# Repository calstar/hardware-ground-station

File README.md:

View this project on [CADLAB.io](https://cadlab.io/project/22830). 

# hardware-ground-station

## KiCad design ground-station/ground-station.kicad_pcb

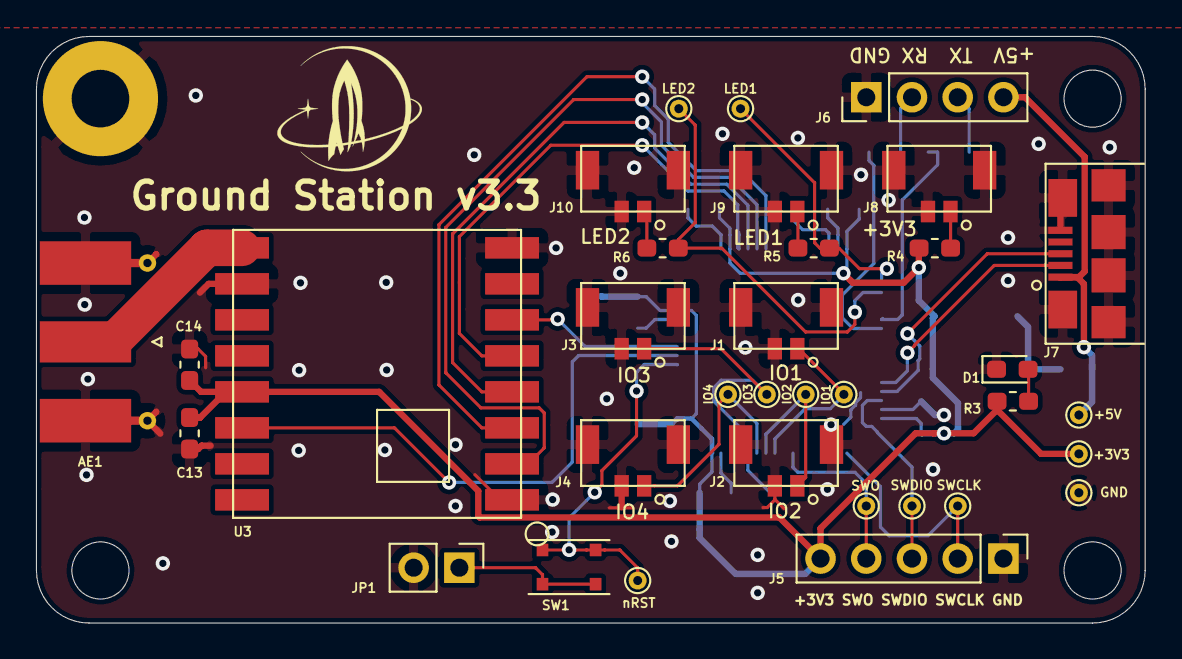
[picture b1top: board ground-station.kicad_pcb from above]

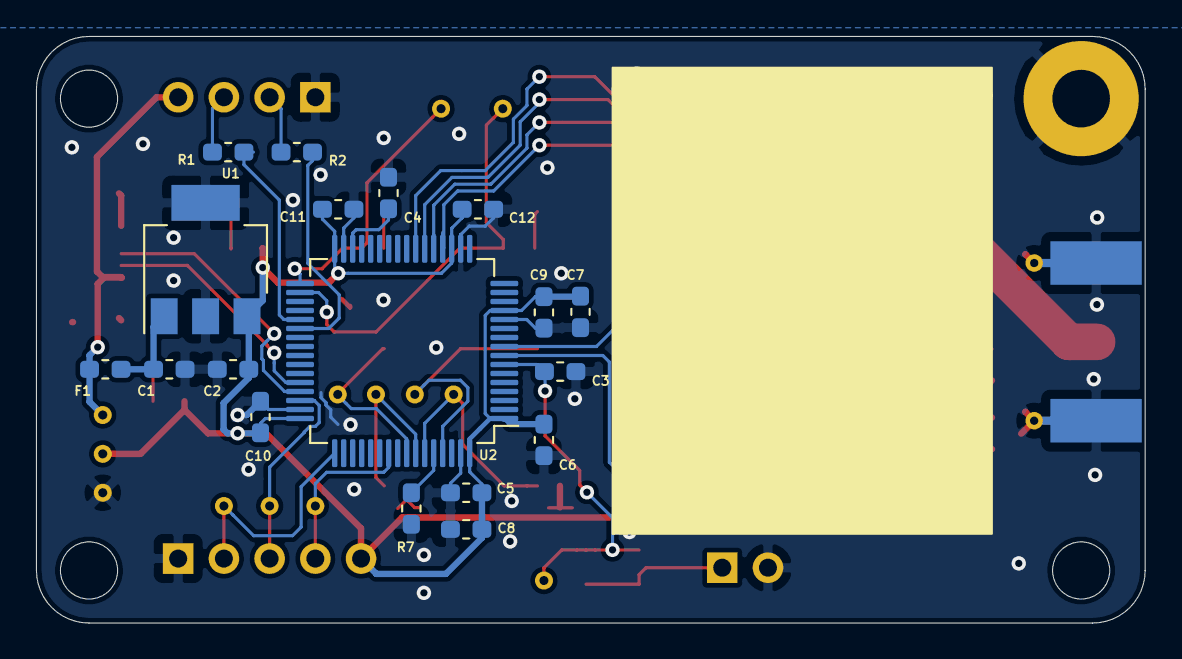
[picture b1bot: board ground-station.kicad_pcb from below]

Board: 2 copper layers, 61.6 x 32.6 mm, 53 parts (18 on the bottom side), 34 nets.

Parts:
AE1: Antenna_Dipole; SMA_Molex_73251-1153_EdgeMount_Horizontal
C1: 0.47uF; C_0603_1608Metric_Pad1.05x0.95mm_HandSolder
C2: 47uF; C_0603_1608Metric_Pad1.05x0.95mm_HandSolder
C3, C6, C7, C8, C10, C11, C12, C14: 0.1uF; C_0603_1608Metric_Pad1.05x0.95mm_HandSolder
C4: 4.7uF; C_0603_1608Metric_Pad1.05x0.95mm_HandSolder
C5, C13: 10uF; C_0603_1608Metric_Pad1.05x0.95mm_HandSolder
C9: 1uF; C_0603_1608Metric_Pad1.05x0.95mm_HandSolder
D1: LED; LED_0603_1608Metric_Pad1.05x0.95mm_HandSolder
F1: Fuse; Fuse_0603_1608Metric_Pad1.05x0.95mm_HandSolder
J1, J2, J3, J4, J8, J9, J10: Conn_01x02; Molex_Micro-Lock_505568-0271_1x02_P1.25mm_Vertical
J5: Conn_01x05; PinHeader_1x05_P2.54mm_Vertical
J6: Conn_01x04; PinHeader_1x04_P2.54mm_Vertical
J7: USB_B_Micro; USB_Micro-B_Amphenol_10118192-0001LF_Horizontal
JP1: Jumper; PinHeader_1x02_P2.54mm_Vertical
Mounting Hole: MountingHole_3.2mm_M3_Pad
R1, R2: 330; R_0603_1608Metric_Pad1.05x0.95mm_HandSolder
R3, R4, R5, R6: 68; R_0603_1608Metric_Pad1.05x0.95mm_HandSolder
R7: 10K; R_0603_1608Metric_Pad1.05x0.95mm_HandSolder
SW1: SW_Push; TE_Button_USLPT3026
TP1, TP2, TP3, TP4, TP13, TP14, TP15, TP16, TP17, TP18, TP19, TP20, TP21: TestPoint; TestPoint_THTPad_D1.0mm_Drill0.5mm
U1: LM3940; SOT-223
U2: STM32F401RETx; LQFP-64_10x10mm_P0.5mm
U3: RFM69HCW

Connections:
+3V3: C2.1, C5.1, C6.1, C7.1, C8.1, C9.1, C10.1, C11.1, C12.1, C13.1, C14.1, J5.5, R3.2, R4.2, TP3.1, U1.3, U2.1, U2.13, U2.19, U2.32, U2.48, U2.64, U3.13
+5V: F1.2, J6.4, J7.1, TP2.1
/RFM69HCW/ANT: AE1.1, U3.9
GND: AE1.2, C1.2, C2.2, C3.2, C4.2, C5.2, C6.2, C7.2, C8.2, C9.2, C10.2, C11.2, C12.2, C13.2, C14.2, D1.1, J1.2, J2.2, J3.2, J4.2, J5.1, J6.1, J7.5, J7.6, J8.2, J9.2, J10.2, JP1.2, Mounting Hole.1, R7.2, TP1.1, U1.2, U1.4, U2.12, U2.18, U2.31, U2.47, U2.63, U3.1, U3.8, U3.10
IO1: J1.1, TP18.1, U2.57
IO2: J2.1, TP19.1, U2.58
IO3: J3.1, TP20.1, U2.61
IO4: J4.1, TP21.1, U2.59
LED1: R5.2, TP16.1, U2.33
LED2: R6.2, TP17.1, U2.34
MCU_RX: R2.2, U2.38
MCU_TX: R1.2, U2.37
unnamed: C1.1, F1.1, U1.1
unnamed: C4.1, U2.30
unnamed: D1.2, R3.1
unnamed: J6.2, R2.1
unnamed: J6.3, R1.1
unnamed: J8.1, R4.1
unnamed: J9.1, R5.1
unnamed: J10.1, R6.1
unnamed: JP1.1, SW1.2
unnamed: R7.1, U2.60
OTG_FS_D+: J7.3, U2.45
OTG_FS_D-: J7.2, U2.44
RadioINT: U2.8, U3.14
RadioMISO: U2.22, U3.2
RadioMOSI: U2.23, U3.3
RadioRST: U2.9, U3.6
RadioSCK: U2.21, U3.4
RadionSS: U2.20, U3.5
SWCLK: J5.2, TP15.1, U2.49
SWDIO: J5.3, TP14.1, U2.46
SWO: J5.4, TP13.1, U2.55
nRST: C3.1, SW1.1, TP4.1, U2.7

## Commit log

2019-12-01 most of schematic
2019-12-01 Backlink to CADLAB.io has been added.
2019-12-01 added test points and organized schematic
2019-12-01 created footprints for rfm, usb micro b, and sma, and assigned all footprints
2019-12-08 lots of work on layout + change button to compact button
2019-12-31 mounting holes, more uniform connectors
2019-12-31 silkscreen
2020-01-04 changes from first review from aled and rajiv
2020-01-28 shorted radio SPI traces on back layer
2020-02-02 slight adjustments to increase ground plane
2020-02-28 silkscreen and logos
